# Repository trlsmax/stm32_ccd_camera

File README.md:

# stm32_ccd_camera
A STM32 CCD camera

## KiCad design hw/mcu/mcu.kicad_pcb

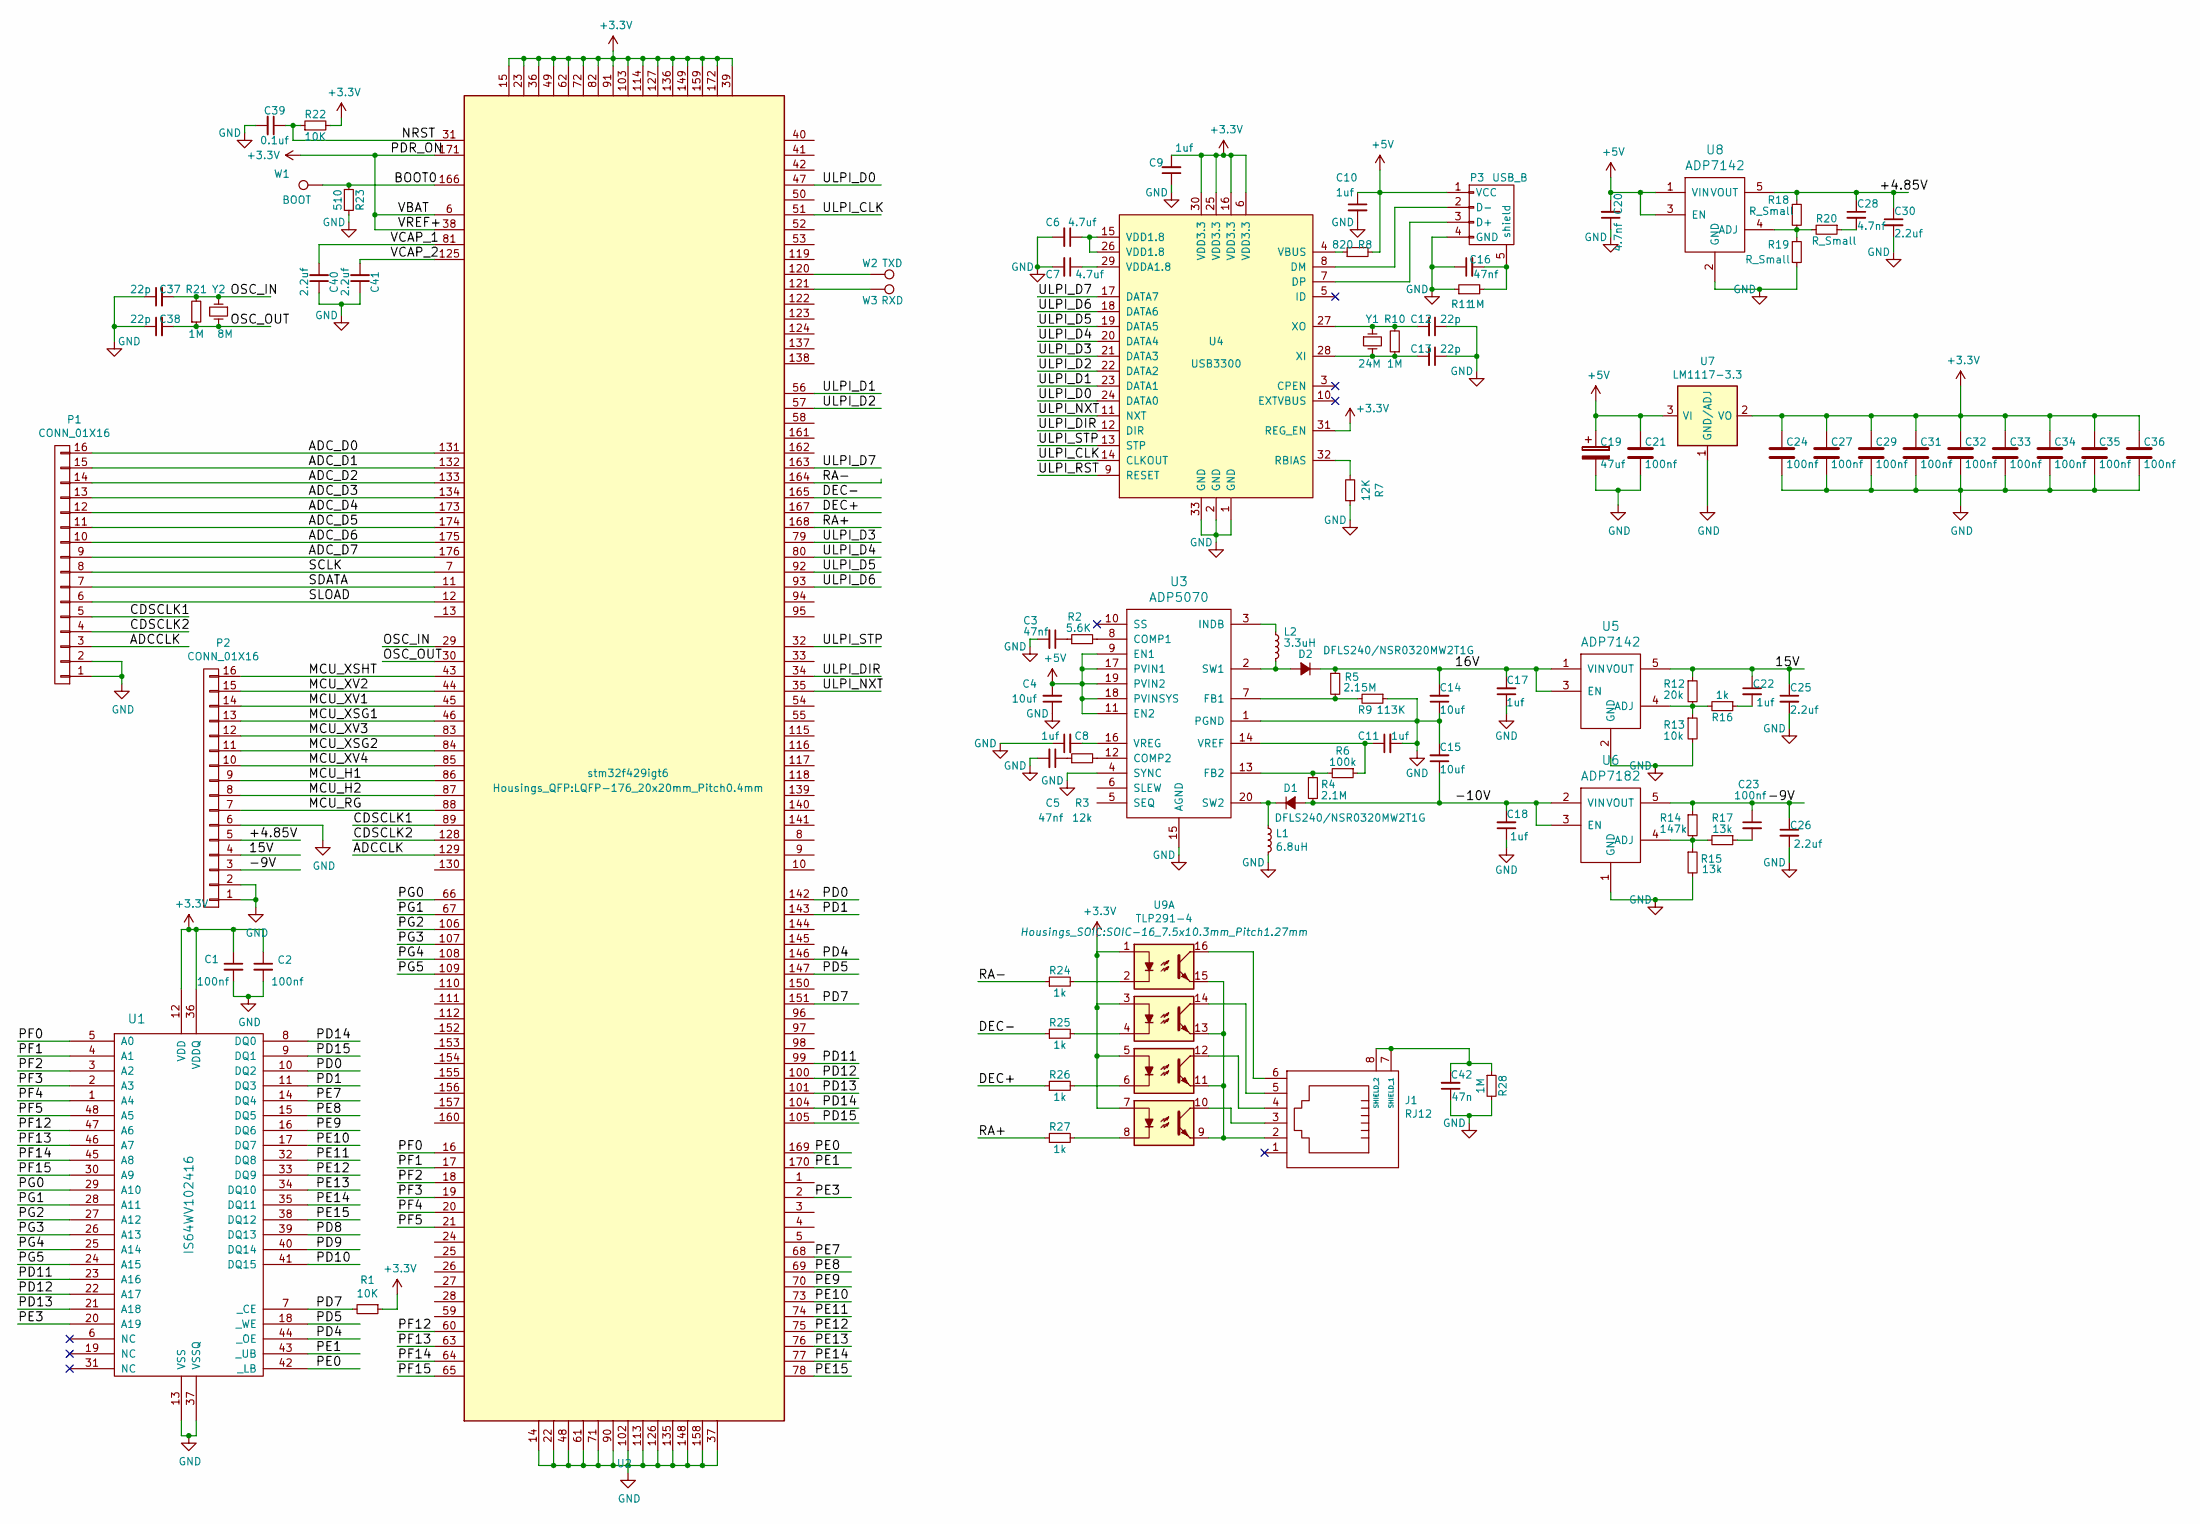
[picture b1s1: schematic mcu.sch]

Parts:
C1, C2, C21, C23, C24, C27, C29, C31, C32, C33, C34, C35, C36: 100nf; C_0603
C3, C5, C16: 47nf; C_0603
C4: 10uf; C_1206
C6, C7: 4.7uf; C_0603
C8, C9, C10, C11, C17, C18, C22: 1uf; C_0603
C12, C13, C37, C38: 22p; C_0603
C14, C15: 10uf; C_0603
C19: 47uf; c_elec_4x5.3
C20, C28: 4.7nf; C_0603
C25, C26, C30, C40, C41: 2.2uf; C_0603
C39: 0.1uf; C_0603
C42: 47n; C_0603
D1, D2: DFLS240/NSR0320MW2T1G; SOD-323
J1: RJ12; RJ12_EQMAX
L1: 6.8uH; Choke_SMD_3x3_H1.5
L2: 3.3uH; Choke_SMD_3x3_H1.5
P1, P2: CONN_01X16; FPC_16
P3: USB_B
R1, R22: 10K; R_0603
R2: 5.6K; R_0603
R3: 12k; R_0603
R4: 2.1M; R_0603
R5: 2.15M; R_0603
R6: 100k; R_0603
R7: 12K; R_0603
R8: 820; R_0603
R9: 113K; R_0603
R10, R11, R21, R28: 1M; R_0603
R12: 20k; R_0603
R13: 10k; R_0603
R14: 147k; R_0603
R15, R17: 13k; R_0603
R16, R24, R25, R26, R27: 1k; R_0603
R18, R19, R20: R_Small; R_0603
R23: 510; R_0603
U1: IS64WV102416; TSSOP_48_12X20mm_Pitch0.5mm
U2: stm32f429igt6; LQFP-176_20x20mm_Pitch0.4mm
U3: ADP5070; TSSOP-20_4.4x6.5mm_Pitch0.65mm
U4: USB3300; QFN-32-1EP_5x5mm_Pitch0.5mm
U5, U8: ADP7142; SOT-23-5
U6: ADP7182; SOT-23-5
U7: LM1117-3.3; SOT-223
U9: TLP291-4; SOIC-16_7.5x10.3mm_Pitch1.27mm
W1: BOOT; TP_SMD
W2: TXD; TP_SMD
W3: RXD; TP_SMD
Y1: 24M; Crystal_FOX-FE_SMD
Y2: 8M; Crystal_FOX-FE_SMD

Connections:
+3V3: C1.1, C2.1, C9.2, C24.1, C27.1, C29.1, C31.1, C32.1, C33.1, C34.1, C35.1, C36.1, R1.1, R22.2, U1.12 (VDD), U1.36 (VDDQ), U2.6 (VBAT), U2.15 (VDD), U2.23 (VDD), U2.36 (VDD), U2.38 (VREF+), U2.39 (VDDA), U2.49 (VDD), U2.62 (VDD), U2.72 (VDD), U2.82 (VDD), U2.91 (VDD), U2.103 (VDD), U2.114 (VDD), U2.127 (VDD), U2.136 (VDD), U2.149 (VDD), U2.159 (VDD), U2.171 (PDR_ON), U2.172 (VDD), U4.6 (VDD3.3), U4.16 (VDD3.3), U4.25 (VDD3.3), U4.30 (VDD3.3), U4.31 (REG_EN), U7.2 (VO), U7.4 (VO), U9.1, U9.3, U9.5, U9.7
+5V: C4.2, C10.1, C19.1, C20.2, C21.1, P3.1 (VCC), R8.2, U3.9 (EN1), U3.11 (EN2), U3.17 (PVIN1), U3.18 (PVINSYS), U3.19 (PVIN2), U7.3 (VI), U8.1 (VIN), U8.3 (EN)
/15V: C22.1, C25.1, P2.4, R12.1, U5.5 (VOUT)
/16V: C14.2, C17.2, D2.1 (K), R5.1, U5.1 (VIN), U5.3 (EN)
/+4.85V: C28.1, C30.1, P2.5, R18.1, U8.5 (VOUT)
/-9V: C23.1, C26.1, P2.3, R14.1, U6.5 (VOUT)
/-10V: C15.1, C18.2, D1.2 (A), R4.2, U6.2 (VIN), U6.3 (EN)
/ADCCLK: P1.3, U2.129 (PH14/DCMI_D4/TIM8_CH2N)
/ADC_D0: P1.16, U2.131 (PI0/DCMI_D13/I2S2_WS/SPI2_NSS/TIM5_CH4)
/ADC_D1: P1.15, U2.132 (PI1/DCMI_D8/I2S2_CK/SPI2_SCK)
/ADC_D2: P1.14, U2.133 (PI2/DCMI_D9/I2S2_ext_SD/SPI2_MISO/TIM8_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)
/ADC_D3: P1.13, U2.134 (PI3/DCMI_D10/I2S2_SD/SPI2_MOSI/TIM8_ETR)
/ADC_D4: P1.12, U2.173 (PI4/DCMI_D5/TIM8_BKIN)
/ADC_D5: P1.11, U2.174 (PI5/DCMI_VSYNC/TIM8_CH1)
/ADC_D6: P1.10, U2.175 (PI6/DCMI_D6/TIM8_CH2)
/ADC_D7: P1.9, U2.176 (PI7/DCMI_D7/TIM8_CH3)
/BOOT0: R23.1, U2.166 (BOOT0), W1.1
/CDSCLK1: P1.5, U2.89 (PH12/DCMI_D3/TIM5_CH3)
/CDSCLK2: P1.4, U2.128 (PH13/CAN1_TX/TIM8_CH1N)
/DEC+: R26.1, U2.167 (CAN1_RX/DCMI_D6/ETH_TXD3/I2C1_SCL/SDIO_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)
/DEC-: R25.1, U2.165 (DCMI_VSYNC/FSMC_NL/I2C1_SDA/TIM4_CH2/US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)
/MCU_H1: P2.9, U2.86 (PH9/DAC_EXTI9/DCMI_D0/I2C3_SMBA/TIM12_C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)
/MCU_H2: P2.8, U2.87 (PH10/DCMI_D1/TIM5_CH1)
/MCU_RG: P2.7, U2.88 (PH11/ADC1_EXTI11/ADC2_EXTI11/ADC3_EXTI1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)
/MCU_XSG1: P2.13, U2.46 (PH5/I2C2_SDA)
/MCU_XSG2: P2.11, U2.84 (PH7/ETH_RXD3/I2C3_SCL)
/MCU_XSHT: P2.16, U2.43 (PH2/ETH_CRS)
/MCU_XV1: P2.14, U2.45 (PH4/I2C2_SCL/USB_OTG_HS_ULPI_NXT)
/MCU_XV2: P2.15, U2.44 (PH3/ETH_COL)
/MCU_XV3: P2.12, U2.83 (PH6/ETH_RXD2/I2C2_SMBA/TIM12_CH1)
/MCU_XV4: P2.10, U2.85 (PH8/DCMI_HSYNC/I2C3_SDA)
/NRST: C39.1, R22.1, U2.31 (NRST)
/OSC_IN: C37.2, R21.2, U2.29 (PH0/RCC_OSC_IN), Y2.1
/OSC_OUT: C38.2, R21.1, U2.30 (PH1/RCC_OSC_OUT), Y2.2
/PD0: U1.10 (DQ2), U2.142 (CAN1_RX/FSMC_D2/FSMC_DA2/PD0)
/PD1: U1.11 (DQ3), U2.143 (CAN1_TX/FSMC_D3/FSMC_DA3/PD1)
/PD4: U1.44 (_OE), U2.146 (FSMC_NOE/USART2_RTS/PD4)
/PD5: U1.18 (_WE), U2.147 (FSMC_NWE/USART2_TX/PD5)
/PD7: R1.2, U1.7 (_CE), U2.151 (FSMC_NCE2/FSMC_NE1/USART2_CK/PD7)
/PD11: U1.23 (A16), U2.99 (ADC1_EXTI11/ADC2_EXTI11/ADC3_EXTI11/FSM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)
/PD12: U1.22 (A17), U2.100 (FSMC_A17/FSMC_ALE/TIM4_CH1/USART3_RTS/P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)
/PD13: U1.21 (A18), U2.101 (FSMC_A18/TIM4_CH2/PD13)
/PD14: U1.8 (DQ0), U2.104 (FSMC_D0/FSMC_DA0/TIM4_CH3/PD14)
/PD15: U1.9 (DQ1), U2.105 (ADC1_EXTI15/ADC2_EXTI15/ADC3_EXTI15/FSM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)
/PE0: U1.42 (_LB), U2.169 (DCMI_D2/FSMC_NBL0/TIM4_ETR/PE0)
/PE1: U1.43 (_UB), U2.170 (DCMI_D3/FSMC_NBL1/PE1)
/PE3: U1.20 (A19), U2.2 (FSMC_A19/SYS_TRACED0/PE3)
/PE7: U1.14 (DQ4), U2.68 (FSMC_D4/FSMC_DA4/TIM1_ETR/PE7)
/PE8: U1.15 (DQ5), U2.69 (FSMC_D5/FSMC_DA5/TIM1_CH1N/PE8)
/PE9: U1.16 (DQ6), U2.70 (DAC_EXTI9/FSMC_D6/FSMC_DA6/TIM1_CH1/PE9)
/PE10: U1.17 (DQ7), U2.73 (FSMC_D7/FSMC_DA7/TIM1_CH2N/PE10)
/PE11: U1.32 (DQ8), U2.74 (ADC1_EXTI11/ADC2_EXTI11/ADC3_EXTI11/FSM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)
/PE12: U1.33 (DQ9), U2.75 (FSMC_D9/FSMC_DA9/TIM1_CH3N/PE12)
/PE13: U1.34 (DQ10), U2.76 (FSMC_D10/FSMC_DA10/TIM1_CH3/PE13)
/PE14: U1.35 (DQ11), U2.77 (FSMC_D11/FSMC_DA11/TIM1_CH4/PE14)
/PE15: U1.38 (DQ12), U2.78 (ADC1_EXTI15/ADC2_EXTI15/ADC3_EXTI15/FSM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)
/PF0: U1.5 (A0), U2.16 (PF0/FSMC_A0/I2C2_SDA)
/PF1: U1.4 (A1), U2.17 (PF1/FSMC_A1/I2C2_SCL)
/PF2: U1.3 (A2), U2.18 (PF2/FSMC_A2/I2C2_SMBA)
/PF3: U1.2 (A3), U2.19 (PF3/ADC3_IN9/FSMC_A3)
/PF4: U1.1 (A4), U2.20 (PF4/ADC3_IN14/FSMC_A4)
/PF5: U1.48 (A5), U2.21 (PF5/ADC3_IN15/FSMC_A5)
/PF12: U1.47 (A6), U2.60 (PF12/FSMC_A6)
/PF13: U1.46 (A7), U2.63 (PF13/FSMC_A7)
/PF14: U1.45 (A8), U2.64 (PF14/FSMC_A8)
/PF15: U1.30 (A9), U2.65 (PF15/ADC1_EXTI15/ADC2_EXTI15/ADC3_EXTI1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)
/PG0: U1.29 (A10), U2.66 (PG0/FSMC_A10)
/PG1: U1.28 (A11), U2.67 (PG1/FSMC_A11)
/PG2: U1.27 (A12), U2.106 (PG2/FSMC_A12)
/PG3: U1.26 (A13), U2.107 (PG3/FSMC_A13)
/PG4: U1.25 (A14), U2.108 (PG4/FSMC_A14)
/PG5: U1.24 (A15), U2.109 (PG5/FSMC_A15)
/RA+: R27.1, U2.168 (CAN1_TX/DAC_EXTI9/DCMI_D7/I2C1_SDA/I2S2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)
/RA-: R24.1, U2.164 (CAN2_TX/DCMI_D5/I2C1_SCL/TIM4_CH1/USART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)
/SCLK: P1.8, U2.7 (PI8/RTC_AF2)
/SDATA: P1.7, U2.11 (PI9/CAN1_RX/DAC_EXTI9)
/SLOAD: P1.6, U2.12 (PI10/ETH_RX_ER)
/ULPI_CLK: U2.51 (ADC1_IN5/ADC2_IN5/DAC_OUT2/SPI1_SCK/TIM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), U4.14 (CLKOUT)
/ULPI_D0: U2.47 (ADC1_IN3/ADC2_IN3/ADC3_IN3/ETH_COL/TIM2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), U4.24 (DATA0)
/ULPI_D1: U2.56 (ADC1_IN8/ADC2_IN8/ETH_RXD2/TIM1_CH2N/TI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), U4.23 (DATA1)
/ULPI_D2: U2.57 (ADC1_IN9/ADC2_IN9/ETH_RXD3/TIM1_CH3N/TI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), U4.22 (DATA2)
/ULPI_D3: U2.79 (ETH_RX_ER/I2C2_SCL/I2S2_CK/SPI2_SCK/TIM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), U4.21 (DATA3)
/ULPI_D4: U2.80 (ADC1_EXTI11/ADC2_EXTI11/ADC3_EXTI11/ETH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), U4.20 (DATA4)
/ULPI_D5: U2.92 (CAN2_RX/ETH_TXD0/I2C2_SMBA/I2S2_WS/SPI2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), U4.19 (DATA5)
/ULPI_D6: U2.93 (CAN2_TX/ETH_TXD1/I2S2_CK/SPI2_SCK/TIM1_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), U4.18 (DATA6)
/ULPI_D7: U2.163 (CAN2_RX/DCMI_D10/ETH_PPS_OUT/I2C1_SMBA/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), U4.17 (DATA7)
/ULPI_DIR: U2.34 (ADC1_IN12/ADC2_IN12/ADC3_IN12/ETH_TXD2/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), U4.12 (DIR)
/ULPI_NXT: U2.35 (ADC1_IN13/ADC2_IN13/ADC3_IN13/ETH_TX_CL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), U4.11 (NXT)
/ULPI_STP: U2.32 (ADC1_IN10/ADC2_IN10/ADC3_IN10/USB_OTG_H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), U4.13 (STP)
/VCAP_1: C40.2, U2.81 (VCAP_1)
/VCAP_2: C41.2, U2.125 (VCAP_2)
GND: C1.2, C2.2, C3.2, C4.1, C5.2, C6.2, C7.2, C8.1, C9.1, C10.2, C11.2, C12.1, C13.1, C14.1, C15.2, C16.1, C17.1, C18.1, C19.2, C20.1, C21.2, C24.2, C25.2, C26.2, C27.2, C29.2, C30.2, C31.2, C32.2, C33.2, C34.2, C35.2, C36.2, C37.1, C38.1, C39.2, C40.1, C41.1, C42.1, L1.2, P1.1, P1.2, P2.1, P2.2, P2.6, P3.4 (GND), R7.1, R9.1, R11.1, R13.2, R15.2, R19.2, R23.2, R28.2, U1.13 (VSS), U1.37 (VSSQ), U2.14 (VSS), U2.22 (VSS), U2.37 (VSSA), U2.48 (VSS), U2.61 (VSS), U2.71 (VSS), U2.90 (VSS), U2.102 (VSS), U2.113 (VSS), U2.126 (VSS), U2.135 (VSS), U2.148 (VSS), U2.158 (VSS), U3.1 (PGND), U3.4 (SYNC), U3.15 (AGND), U4.1 (GND), U4.2 (GND), U4.33 (GND), U5.2 (GND), U6.1 (GND), U7.1 (GND/ADJ), U8.2 (GND)
unnamed: C3.1, R2.1
unnamed: C5.1, R3.1
unnamed: C6.1, U4.15 (VDD1.8), U4.26 (VDD1.8)
unnamed: C7.1, U4.29 (VDDA1.8)
unnamed: C8.2, U3.16 (VREG)
unnamed: C11.1, R6.1, U3.14 (VREF)
unnamed: C12.2, R10.2, U4.27 (XO), Y1.1
unnamed: C13.2, R10.1, U4.28 (XI), Y1.2
unnamed: C16.2, P3.5 (shield), R11.2
unnamed: C22.2, R16.1
unnamed: C23.2, R17.1
unnamed: C28.2, R20.1
unnamed: C42.2, J1.7 (SHIELD_1), J1.8 (SHIELD_2), R28.1
unnamed: D1.1 (K), L1.1, U3.20 (SW2)
unnamed: D2.2 (A), L2.2, U3.2 (SW1)
unnamed: J1.2, U9.9, U9.11, U9.13, U9.15
unnamed: J1.3, U9.10
unnamed: J1.4, U9.12
unnamed: J1.5, U9.14
unnamed: J1.6, U9.16
unnamed: L2.1, U3.3 (INDB)
unnamed: P3.2 (D-), U4.8 (DM)
unnamed: P3.3 (D+), U4.7 (DP)
unnamed: R2.2, U3.8 (COMP1)
unnamed: R3.2, U3.12 (COMP2)
unnamed: R4.1, R6.2, U3.13 (FB2)
unnamed: R5.2, R9.2, U3.7 (FB1)
unnamed: R7.2, U4.32 (RBIAS)
unnamed: R8.1, U4.4 (VBUS)
unnamed: R12.2, R13.1, R16.2, U5.4 (ADJ)
unnamed: R14.2, R15.1, R17.2, U6.4 (ADJ)
unnamed: R18.2, R19.1, R20.2, U8.4 (ADJ)
unnamed: R24.2, U9.2
unnamed: R25.2, U9.4
unnamed: R26.2, U9.6
unnamed: R27.2, U9.8
unnamed: U2.120 (DAC_EXTI9/DCMI_D0/I2C3_SMBA/TIM1_CH2/US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), W2.1
unnamed: U2.121 (DCMI_D1/TIM1_CH3/USART1_RX/USB_OTG_FS_I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), W3.1

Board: 2 copper layers, 92 parts (0 on the bottom side), 130 nets, no tracks yet.

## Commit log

2016-12-07 init add hardware
2016-12-13 add pdf sch
